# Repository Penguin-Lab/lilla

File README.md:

# lilla
A Lilla é uma robô quadrúpede desenvolvida para andar de forma autônoma ou para ser controlada pelo celular. Para se locomover, ela possui 4 patas de 3 graus de liberdade cada (3 motores) e uma ESP32 que comanda o conjunto! Ela é a quarta integrante robótica do nosso espaço inteligente!

# Estrutura física
A estrutura física do robô é composta por quatro patas de três eixos cada (três motores). As patas são fixadas a uma estrutura de PLA para deixar o robô firme. As peças são todas projetadas em 3D e foram impressas utilizando PLA, podendo ser encontradas na pasta Pecas_3d deste projeto.

## Peças 3D em STL
As peças em 3D desenvolvidas para este projeto foram baseadas no projeto do robô desenvolvido por Andres ([LINK](https://gitlab.com/anflores/pavlov_mini)). Na pasta Pecas_3d, estão listadas essas peças em STL. Para ajudar, segue abaixo uma lista de todas as peças que devem ser impressas e qual o valor da sua maior dimensão (para ajudar na escolha da impressora):
* Corpo
  * 1x [LILLA_AXILA_FRONT_LEFT.STL (81 mm)](https://github.com/Penguin-Lab/lilla/blob/main/Pecas_3d/LILLA_AXILA_FRONT_LEFT.STL)
  * 1x [LILLA_AXILA_FRONT_RIGHT.STL (81 mm)](https://github.com/Penguin-Lab/lilla/blob/main/Pecas_3d/LILLA_AXILA_FRONT_RIGHT.STL)
  * 1x [LILLA_AXILA_BACK_LEFT.STL (81 mm)](https://github.com/Penguin-Lab/lilla/blob/main/Pecas_3d/LILLA_AXILA_BACK_LEFT.STL)
  * 1x [LILLA_AXILA_BACK_RIGHT.STL (81 mm)](https://github.com/Penguin-Lab/lilla/blob/main/Pecas_3d/LILLA_AXILA_BACK_RIGHT.STL)
  * 1x [LILLA_SUPPORT_LEFT_TOP.STL (127 mm)](https://github.com/Penguin-Lab/lilla/blob/main/Pecas_3d/LILLA_SUPPORT_LEFT_TOP.STL)
  * 1x [LILLA_SUPPORT_LEFT_TOP.STL espelhado (127 mm)](https://github.com/Penguin-Lab/lilla/blob/main/Pecas_3d/LILLA_SUPPORT_LEFT_TOP.STL)
  * 2x [LILLA_SUPPORT_FACE_BACK_UP.STL (51 mm)](https://github.com/Penguin-Lab/lilla/blob/main/Pecas_3d/LILLA_SUPPORT_FACE_BACK_UP.STL)
  * 2x [LILLA_SUPPORT_FACE_BACK_DOWN.STL (63 mm)](https://github.com/Penguin-Lab/lilla/blob/main/Pecas_3d/LILLA_SUPPORT_FACE_BACK_DOWN.STL)
  * 2x [LILLA_SUPPORT_FACE_BACK_DOWN.STL (63 mm)](https://github.com/Penguin-Lab/lilla/blob/main/Pecas_3d/LILLA_SUPPORT_FACE_BACK_DOWN.STL)
  * 2x [LILLA_SUPPORT_BOTTOM.STL (99 mm)](https://github.com/Penguin-Lab/lilla/blob/main/Pecas_3d/LILLA_SUPPORT_BOTTOM.STL)
  * 4x [LILLA_SUPPORT_PCI.STL (9 mm)](https://github.com/Penguin-Lab/lilla/blob/main/Pecas_3d/LILLA_SUPPORT_PCI.STL)
* Patas
  * 2x [LILLA_TIBIA_LEFT.STL (128 mm)](https://github.com/Penguin-Lab/lilla/blob/main/Pecas_3d/LILLA_TIBIA_LEFT.STL)
  * 2x [LILLA_TIBIA_LEFT.STL espelhado (128 mm)](https://github.com/Penguin-Lab/lilla/blob/main/Pecas_3d/LILLA_TIBIA_LEFT.STL)
  * 2x [LILLA_FEMUR_LEFT_A_1.STL (134 mm)](https://github.com/Penguin-Lab/lilla/blob/main/Pecas_3d/LILLA_FEMUR_LEFT_A_1.STL)
  * 2x [LILLA_FEMUR_LEFT_A_1.STL espelhado (134 mm)](https://github.com/Penguin-Lab/lilla/blob/main/Pecas_3d/LILLA_FEMUR_LEFT_A_1.STL)
  * 4x [LILLA_FEMUR_LEFT_A_2.STL (8 mm)](https://github.com/Penguin-Lab/lilla/blob/main/Pecas_3d/LILLA_FEMUR_LEFT_A_2.STL)
  * 2x [LILLA_FEMUR_LEFT_B.STL (134 mm)](https://github.com/Penguin-Lab/lilla/blob/main/Pecas_3d/LILLA_FEMUR_LEFT_B.STL)
  * 2x [LILLA_FEMUR_LEFT_B.STL espelhado (134 mm)](https://github.com/Penguin-Lab/lilla/blob/main/Pecas_3d/LILLA_FEMUR_LEFT_B.STL)
  * 2x [LILLA_OMBRO_LEFTFRONT_BACKRIGHT.STL (66 mm)](https://github.com/Penguin-Lab/lilla/blob/main/Pecas_3d/LILLA_OMBRO_LEFTFRONT_BACKRIGHT.STL)
  * 2x [LILLA_OMBRO_LEFTFRONT_BACKRIGHT.STL espelhado (66 mm)](https://github.com/Penguin-Lab/lilla/blob/main/Pecas_3d/LILLA_OMBRO_LEFTFRONT_BACKRIGHT.STL)
  * 8x [LILLA_TIBIA_TUBO.STL (20 mm)](https://github.com/Penguin-Lab/lilla/blob/main/Pecas_3d/LILLA_TIBIA_TUBO.STL)
* Rosto e bumbum
  * 1x [LILLA_FRONT_FRAME.STL (137 mm)](https://github.com/Penguin-Lab/lilla/blob/main/Pecas_3d/LILLA_FRONT_FRAME.STL)
  * 1x [LILLA_FACE.STL (137 mm)](https://github.com/Penguin-Lab/lilla/blob/main/Pecas_3d/LILLA_FACE.STL)
  * 1x [LILLA_BUMBUM.STL (137 mm)](https://github.com/Penguin-Lab/lilla/blob/main/Pecas_3d/LILLA_BUMBUM.STL)

Obs 1: para que as patas girem sem forçar a conexão dos eixos dos motores com as peças, são utilizados dois tipos de rolamentos para cada pata: dois rolamentos [6805-2RS 25x37x7](https://pt.aliexpress.com/item/4000347743665.html?src=google&snpsid=230868174&pdp_npi=4%40dis!BRL!42.29!42.29!!!!!%4021032fb417539812201246724d5fbe!12000025424450961!ppc!!!&snps=y&src=google&albch=shopping&acnt=768-202-3196&isdl=y&slnk=&plac=&mtctp=&albbt=Google_7_shopping&aff_platform=google&aff_short_key=_oEDJ7Ho&gclsrc=aw.ds&&albagn=888888&&ds_e_adid=&ds_e_matchtype=&ds_e_device=c&ds_e_network=x&ds_e_product_group_id=&ds_e_product_id=pt4000347743665&ds_e_product_merchant_id=5551326180&ds_e_product_country=BR&ds_e_product_language=pt&ds_e_product_channel=online&ds_e_product_store_id=&ds_url_v=2&albcp=21532694118&albag=&isSmbAutoCall=false&needSmbHouyi=false&gad_source=1&gad_campaignid=22003973025&gbraid=0AAAAAC_WlP-osBnJpLOe33NXV9Dkw2uHs&gclid=CjwKCAjwqKzEBhANEiwAeQaPVaxBBwSfUmAnXYsZFo7xcrcdahXF7pTrYmLQCVcC5jL9HLM-KAcNBRoCUIAQAvD_BwE) e um rolamentos [606-2RS 6x17x6](https://www.oliveirarolamentos.com.br/micro-rolamento-rigido-de-esferas-606-2rs-c3-6x17x6mm.html?srsltid=AfmBOorIJu8QL9XP75JwG1OypQNvwIxncIfi8yv9wJUTfwy0kq7k5aC4).
Obs 2: para o comando da tibia, o motor deverá ter em seu eixo uma [polia dentada GT2 de 36 dentes para eixo de servo e correia de 6mm](https://a.aliexpress.com/_mPVv40N), e uma [correia de 6mm com 300mm de comprimento](https://a.aliexpress.com/_mN8S5o1).

Obs 3: os outros motores ficam fixados nas peças por [discos metálicos pequenos padrão para eixos de servo](https://a.aliexpress.com/_mPHt3nf).

## Outros itens da estrutura
Alguns outros itens são necessários para finalizar a estrutura da Lilla:
* Parafusos m3 de diversos tamanhos
* 4x Tiras de EVA: colocar na ponta das peças de tibia para evitar que o robô deslize no chão

## Placa de circuito impresso
No projeto, foi desenvolvida uma placa de circuito para servir como shield para a ESP32 e conexão com a placa PCA9685 e o módulo DFPlayer Mini MP3 Player.

## Componentes eletrônicos
Os componentes eletrônicos embarcados no robô e equipamentos utilizados são:
* Controlador com Wi-fi e Bluetooth
  * 1x ESP32 (38 pinos)
* Motores
  * 12x Servo TowerPro MG995 Metálico
* 1x Placa PCA9685 para comando dos 12 motores
* 1x Módulo DFPlayer Mini MP3 Player com cartão micro SD contendo aúdio de latidos
* 1x Alto-falante de 3W e 4Ohm para os latidos
* Chave (switch)
* Alimentação
  * Bateria Zippy LiFe 1100mAh 2s 6,6V (ESP32)
  * Bateria TM Hobbies LiFe 2100mAh 2s 6,6v (motores)

# Software
Na pasta de códigos, há um código de programação da ESP32 (38 pinos). Ele é um exemplo em C++ do comando de movimentação da Lilla:
* Dabble: a ESP32 pode se comunicar com o aplicativo Dabble no celular e receber comandos de ação.

## Alunas participantes e desenvolvedoras da Lilla
* Ana Carolina Domingues Benisio
* Jéssica Kauany Morais Carvalho
* Maria Cecilia poton Cristovão
* Sarah Souza Mendes

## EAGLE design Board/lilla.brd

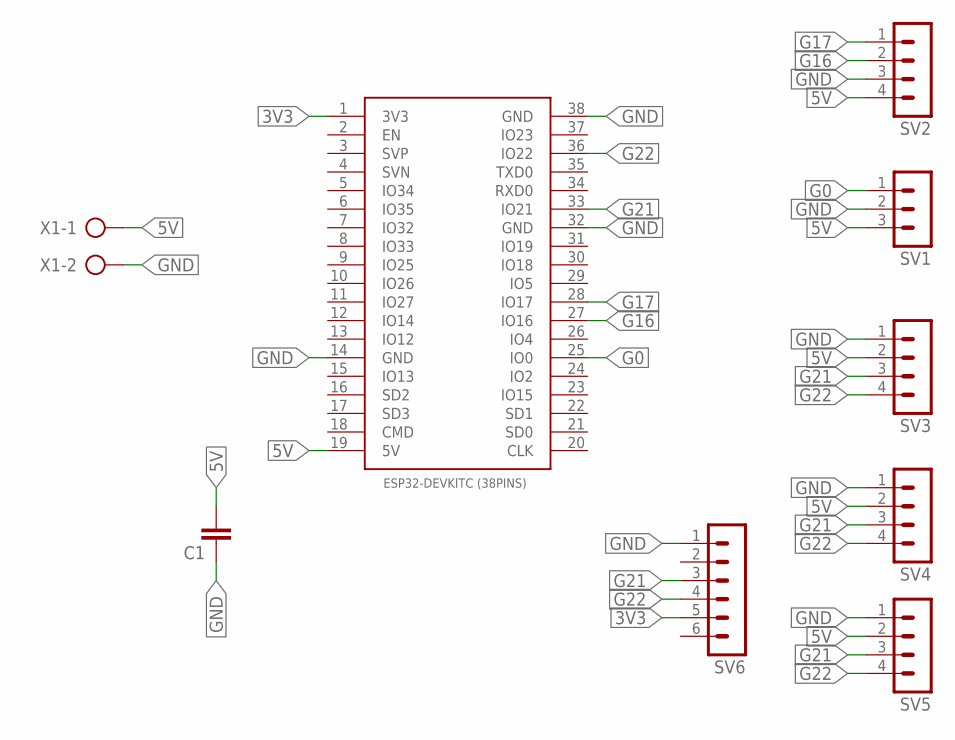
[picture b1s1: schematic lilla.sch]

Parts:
C1: C-EU050-024X044; C050-024X044
ESP32-DEVKITC(38PINS)2: ESP32DEVKITC_38PINS; ESP32-DEVKITC
SV1: MA03-1
SV2, SV3, SV4, SV5: MA04-1
SV6: MA06-1
X1: AK300/2

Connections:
3V3: ESP32-DEVKITC(38PINS)2.1 (3V3), SV6.5
5V: C1.2, ESP32-DEVKITC(38PINS)2.19 (5V), SV1.3, SV2.4, SV3.2, SV4.2, SV5.2, X1.1
G0: ESP32-DEVKITC(38PINS)2.25 (IO0), SV1.1
G16: ESP32-DEVKITC(38PINS)2.27 (IO16), SV2.2
G17: ESP32-DEVKITC(38PINS)2.28 (IO17), SV2.1
G21: ESP32-DEVKITC(38PINS)2.33 (IO21), SV3.3, SV4.3, SV5.3, SV6.3
G22: ESP32-DEVKITC(38PINS)2.36 (IO22), SV3.4, SV4.4, SV5.4, SV6.4
GND: C1.1, ESP32-DEVKITC(38PINS)2.14 (GND), ESP32-DEVKITC(38PINS)2.32 (GND), ESP32-DEVKITC(38PINS)2.38 (GND), SV1.2, SV2.3, SV3.1, SV4.1, SV5.1, SV6.1, X1.2

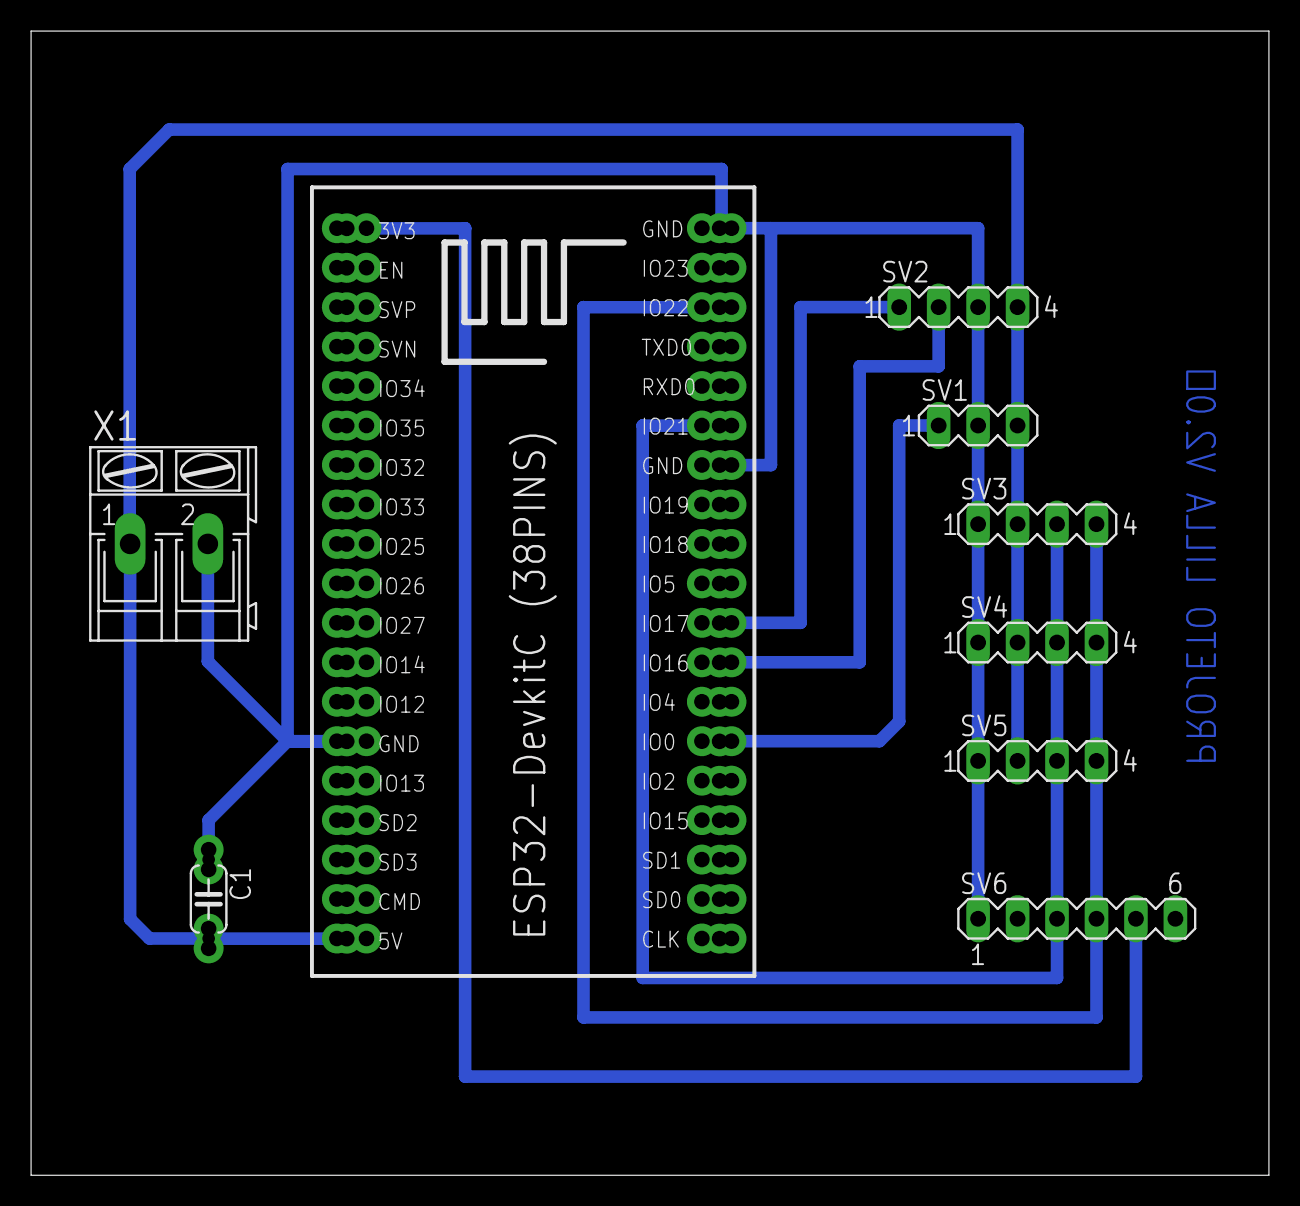
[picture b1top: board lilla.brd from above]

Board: 2 copper layers, 79.7 x 73.7 mm, 9 parts (0 on the bottom side), 8 nets.

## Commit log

2025-07-31 Create Pecas_3d
2025-07-31 Create Codes
2025-07-31 Create images
2025-08-01 Create coisa
2025-08-21 Rename board_lilla_v1.pdf to Board/board_lilla_v1.pdf
2026-03-23 Add touch sensor functionality
